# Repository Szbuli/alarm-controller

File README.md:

# Sensor Controller

## Main Features

- **15 configurable sensor inputs**  
- **Supported power supply:** 13.8 V nominal  
- **Home Assistant autodiscovery** via MQTT gateway
- **Input types supported:**  
  - Alarm sensors with multi-level signaling (e.g., open/tamper detection)  
  - Pulse counters (e.g., utility meters)

## Hardware

- **Microcontroller:** STM32F103R8T6  
- **Non-volatile memory:** MB85RC256V FRAM  
- **CAN Bus Transceiver:** SN65HVD230  
- **Electrical protection:**  
  - Overvoltage-protected inputs  
  - Overload protection circuitry  
- **Debug Interface:** Serial Wire Debug (SWD)

## Development Tools

- **PCB Design:** Autodesk EAGLE  
- **Firmware:** STM32CubeIDE (C via HAL / LL libraries)

## Setup
1. **Assign the device ID** via MQTT topic: `smarthome/alarm_controller/config`
2. **Configure sensor input types**
-- `1` → Alarm sensor
-- `3` → Pulse counter (normally open)
-- `4` → Pulse counter (normally closed)

## Sensor Connection & Security

To ensure reliable operation and tamper detection, each sensor input must be connected using a resistor for end-of-line (EOL) supervision.
The controller uses a voltage divider circuit to distinguish between different sensor states. The correct resistor value is essential for accurate detection:

- **Switch / Door Contact Sensors:**  
  Use a **40.2 kΩ** resistor in series with the sensor contact.  
- **Alarm Sensors:**  
  - **Normal (closed) signal:** ~40 kΩ total resistance  
  - **Alarm (open) signal:** ~140 kΩ total resistance

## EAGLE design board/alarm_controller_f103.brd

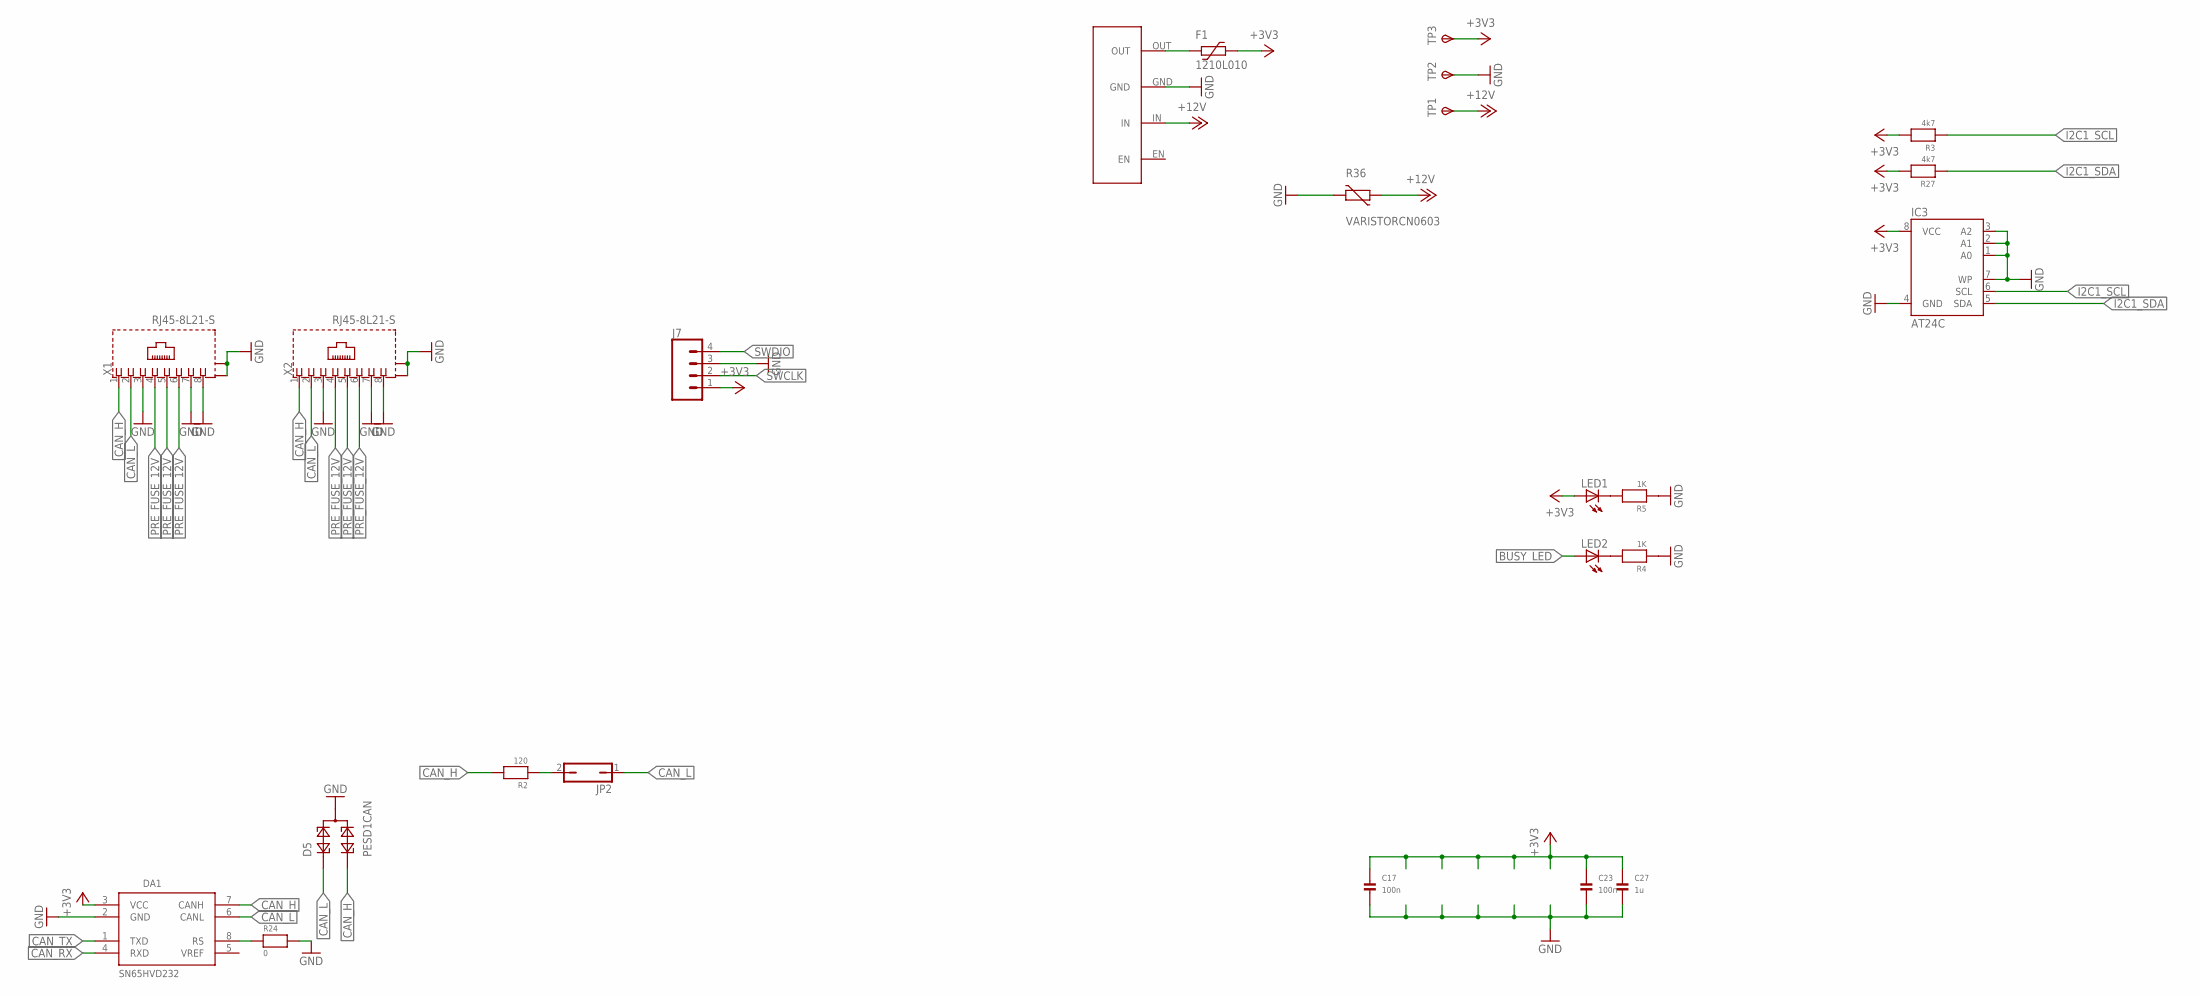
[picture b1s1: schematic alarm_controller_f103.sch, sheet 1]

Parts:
C17, C23: 100n; 0603
C27: 1u; 0603
D5: PESD1CAN; SOT23
DA1: SN65HVD232; SO08
F1: 1210L010; 1210L
IC3: AT24C; SOIC8
J7: CONN_04POLAR_LOCK; MOLEX-1X4_LOCK
JP2: JP1Q; JP1
LED1, LED2: LEDCHIPLED_0805; CHIPLED_0805
R2: 120; 0603
R3, R27: 4k7; 0603
R4, R5: 1K; 0603
R24: 0; 0603
R36: VARISTORCN0603; CT/CN0603
TP1, TP2, TP3: TPSTP20R; TP20R
U$4: HW-613
X1, X2: RJ45-8L21-S; RJ45-SHIELD1

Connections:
+3V3: C17.1, C23.1, C27.1, DA1.3 (VCC), F1.1, IC3.8 (VCC), J7.1, LED1.A, R3.2, R27.2, TP3.TP; also elsewhere on the board
+12V: R36.1, TP1.TP, U$4.IN; also elsewhere on the board
BUSY_LED: LED2.A; also elsewhere on the board
CAN_H: D5.2, DA1.7 (CANH), R2.2, X1.1, X2.1
CAN_L: D5.1, DA1.6 (CANL), JP2.1, X1.2, X2.2
CAN_RX: DA1.4 (RXD); also elsewhere on the board
CAN_TX: DA1.1 (TXD); also elsewhere on the board
GND: C17.2, C23.2, C27.2, D5.3, DA1.2 (GND), IC3.1 (A0), IC3.2 (A1), IC3.3 (A2), IC3.4 (GND), IC3.7 (WP), J7.3, R4.1, R5.1, R24.2, R36.2, TP2.TP, U$4.GND, X1.3, X1.7, X1.8, X1.S1 (S), X1.S2 (S), X2.3, X2.7, X2.8, X2.S1 (S), X2.S2 (S); also elsewhere on the board
I2C1_SCL: IC3.6 (SCL), R3.1; also elsewhere on the board
I2C1_SDA: IC3.5 (SDA), R27.1; also elsewhere on the board
unnamed: F1.2, U$4.OUT
unnamed: LED1.C, R5.2
unnamed: LED2.C, R4.2
unnamed: JP2.2, R2.1
unnamed: DA1.8 (RS), R24.1
PRE_FUSE_12V: X1.4, X1.5, X1.6, X2.4, X2.5, X2.6; also elsewhere on the board
SWCLK: J7.2; also elsewhere on the board
SWDIO: J7.4; also elsewhere on the board

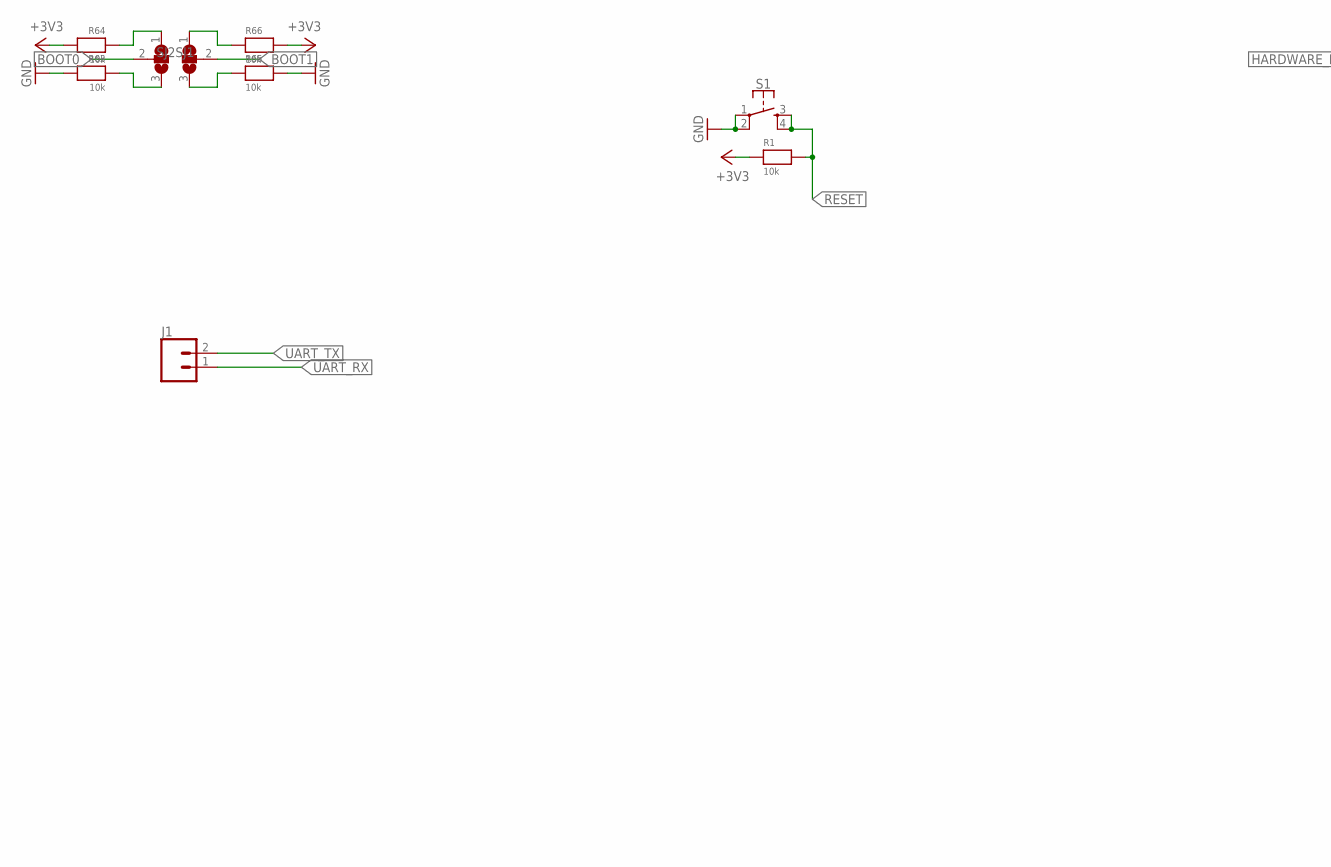
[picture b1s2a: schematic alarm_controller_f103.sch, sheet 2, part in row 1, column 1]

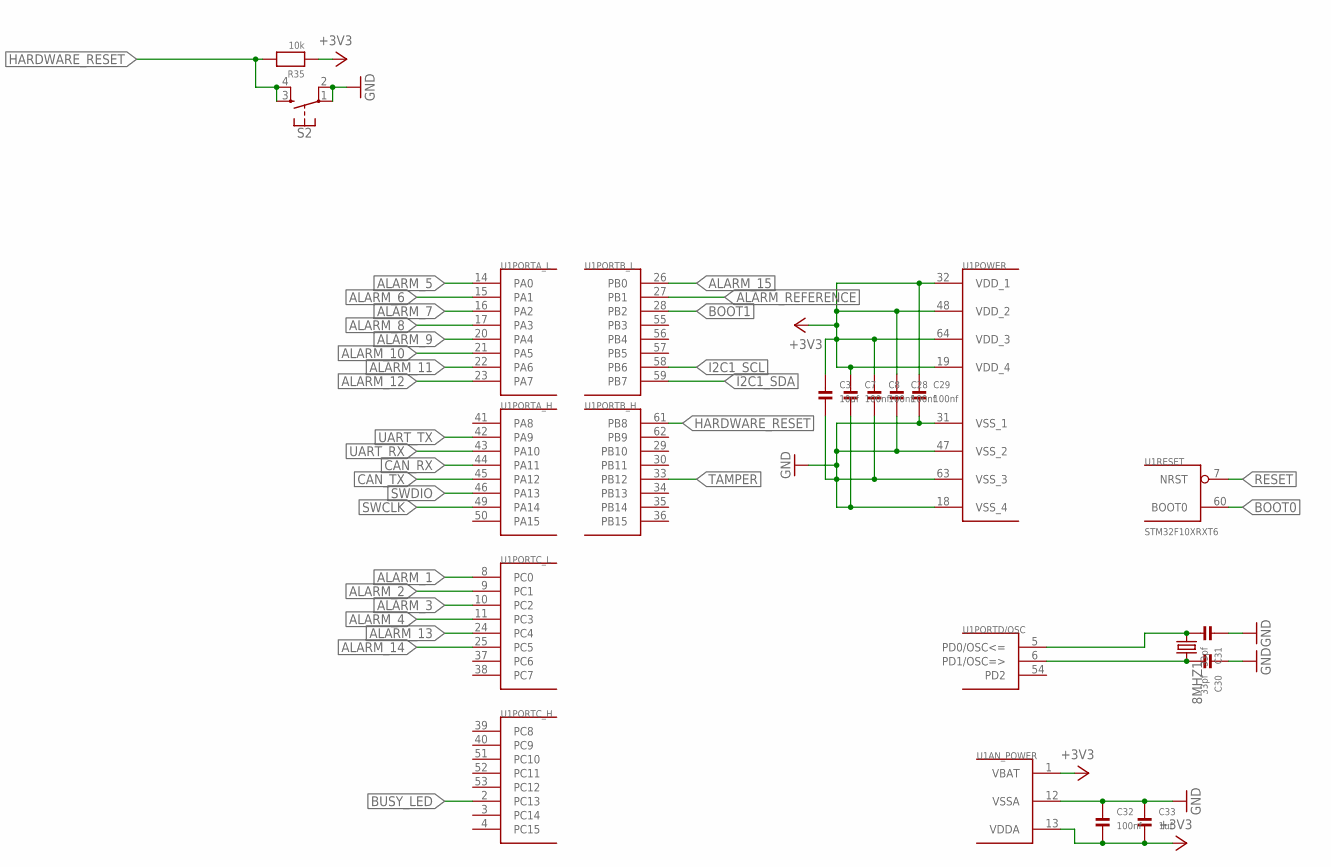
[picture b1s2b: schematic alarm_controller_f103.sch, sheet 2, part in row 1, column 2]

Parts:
8MHZ1: CRYSTALHC49UP; HC49UP
C3: 10uf; 0805
C7, C8, C28, C29, C32: 100nf; 0603-MINI
C30, C31: 33pf; 0603
C33: 1uf; 0603-MINI
J1: CONN_02; 1X02
R1, R35, R63, R64, R65, R66: 10k; 0603
S1, S2: MOMENTARY-SWITCH-SPST-2-SMD-4.6X2.8MM; TACTILE_SWITCH_SMD_4.6X2.8MM
SJ1, SJ2: SJ2W; SJ_2
U1: STM32F10XRXT6; TQFP64

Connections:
+3V3: C3.1, C7.1, C8.1, C28.1, C29.1, C32.2, C33.2, R1.1, R35.1, R64.2, R66.2, U1.1 (VBAT), U1.13 (VDDA), U1.19 (VDD_4), U1.32 (VDD_1), U1.48 (VDD_2), U1.64 (VDD_3); also elsewhere on the board
ALARM_1: U1.8 (PC0); also elsewhere on the board
ALARM_2: U1.9 (PC1); also elsewhere on the board
ALARM_3: U1.10 (PC2); also elsewhere on the board
ALARM_4: U1.11 (PC3); also elsewhere on the board
ALARM_5: U1.14 (PA0); also elsewhere on the board
ALARM_6: U1.15 (PA1); also elsewhere on the board
ALARM_7: U1.16 (PA2); also elsewhere on the board
ALARM_8: U1.17 (PA3); also elsewhere on the board
ALARM_9: U1.20 (PA4); also elsewhere on the board
ALARM_10: U1.21 (PA5); also elsewhere on the board
ALARM_11: U1.22 (PA6); also elsewhere on the board
ALARM_12: U1.23 (PA7); also elsewhere on the board
ALARM_13: U1.24 (PC4); also elsewhere on the board
ALARM_14: U1.25 (PC5); also elsewhere on the board
ALARM_15: U1.26 (PB0); also elsewhere on the board
ALARM_REFERENCE: U1.27 (PB1); also elsewhere on the board
BOOT0: SJ1.2, U1.60 (BOOT0)
BOOT1: SJ2.2, U1.28 (PB2)
BUSY_LED: U1.2 (PC13); also elsewhere on the board
CAN_RX: U1.44 (PA11); also elsewhere on the board
CAN_TX: U1.45 (PA12); also elsewhere on the board
GND: C3.2, C7.2, C8.2, C28.2, C29.2, C30.1, C31.1, C32.1, C33.1, R63.2, R65.2, S1.1, S1.2, S2.1, S2.2, U1.12 (VSSA), U1.18 (VSS_4), U1.31 (VSS_1), U1.47 (VSS_2), U1.63 (VSS_3); also elsewhere on the board
HARDWARE_RESET: R35.2, S2.3, S2.4, U1.61 (PB8)
I2C1_SCL: U1.58 (PB6); also elsewhere on the board
I2C1_SDA: U1.59 (PB7); also elsewhere on the board
unnamed: R66.1, SJ2.1
unnamed: R64.1, SJ1.1
unnamed: R65.1, SJ2.3
unnamed: R63.1, SJ1.3
unnamed: 8MHZ1.2, C30.2, U1.6 (PD1/OSC=>)
unnamed: 8MHZ1.1, C31.2, U1.5 (PD0/OSC<=)
RESET: R1.2, S1.3, S1.4, U1.7 (NRST)
SWCLK: U1.49 (PA14); also elsewhere on the board
SWDIO: U1.46 (PA13); also elsewhere on the board
TAMPER: U1.33 (PB12); also elsewhere on the board
UART_RX: J1.1, U1.43 (PA10)
UART_TX: J1.2, U1.42 (PA9)

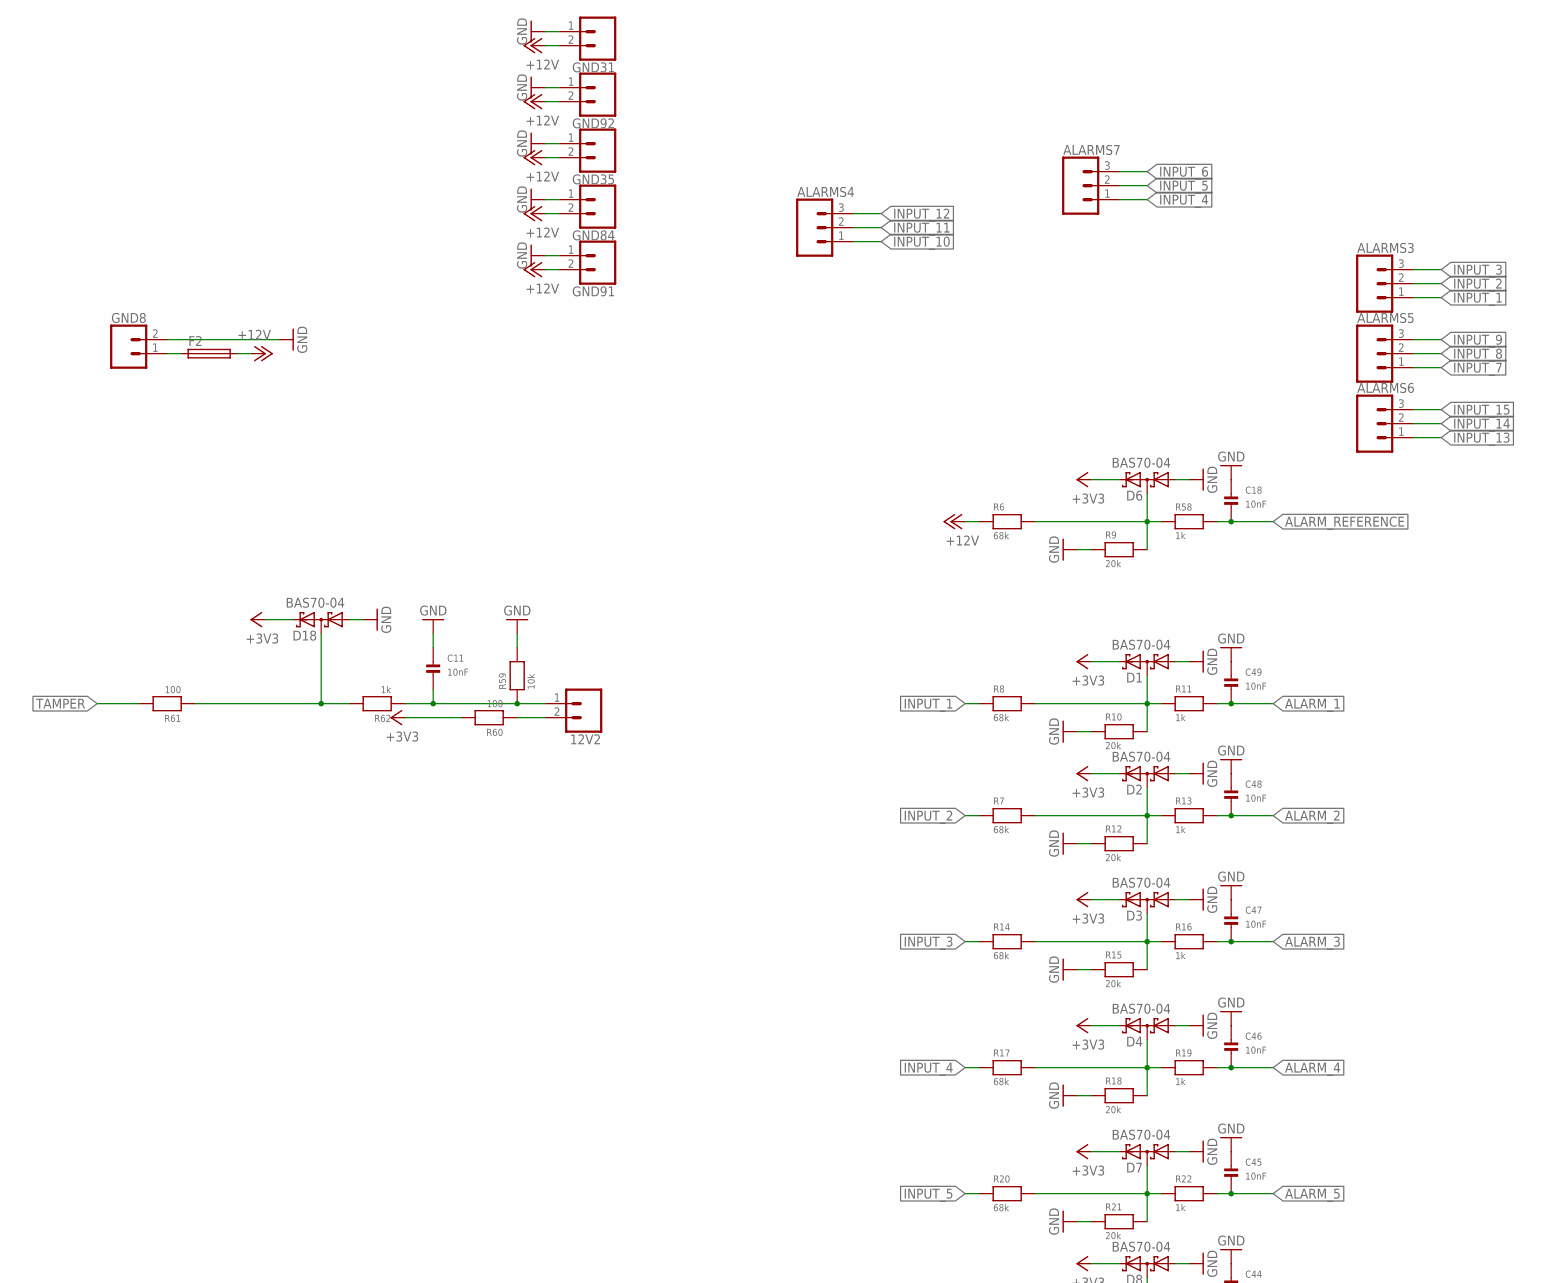
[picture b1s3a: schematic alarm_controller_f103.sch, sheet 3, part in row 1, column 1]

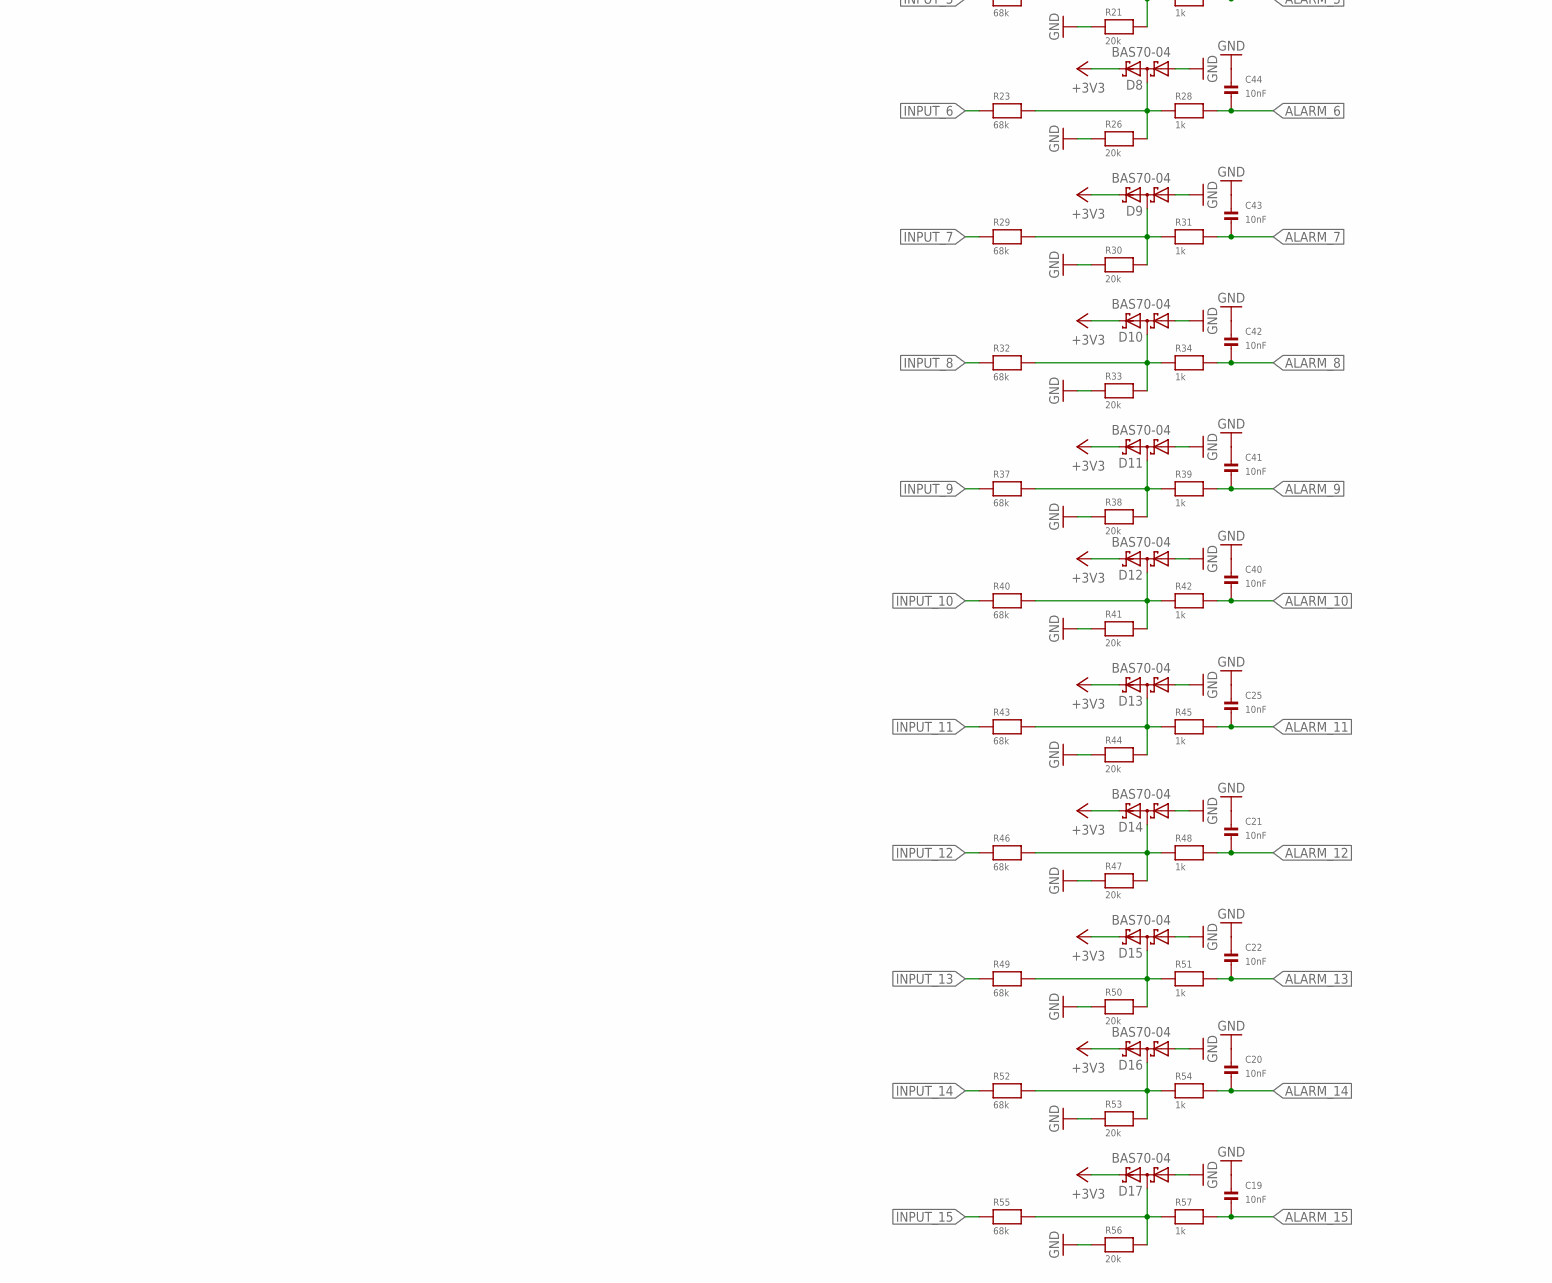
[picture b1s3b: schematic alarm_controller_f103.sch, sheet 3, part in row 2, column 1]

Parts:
12V2: CONN_023.5MM; SCREWTERMINAL-3.5MM-2
ALARMS3, ALARMS4, ALARMS5, ALARMS6, ALARMS7: CONN_03SCREW_LOCK; SCREWTERMINAL-3.5MM-3_LOCK.007S
C11, C18, C19, C20, C21, C22, C25, C40, C41, C42, C43, C44, C45, C46, C47, C48, C49: 10nF; 0603
D1, D2, D3, D4, D6, D7, D8, D9, D10, D11, D12, D13, D14, D15, D16, D17, D18: BAS70-04; SOT23
F2: TE5
GND8: CONN_025MM; SCREWTERMINAL-5MM-2
GND31, GND35, GND84, GND91, GND92: CONN_023.5MM; SCREWTERMINAL-3.5MM-2
R6, R7, R8, R14, R17, R20, R23, R29, R32, R37, R40, R43, R46, R49, R52, R55: 68k; 0603
R9, R10, R12, R15, R18, R21, R26, R30, R33, R38, R41, R44, R47, R50, R53, R56: 20k; 0603
R11, R13, R16, R19, R22, R28, R31, R34, R39, R42, R45, R48, R51, R54, R57, R58, R62: 1k; 0603
R59: 10k; 0603
R60, R61: 100; 0603

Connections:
12V_REFERENCE1: D2.3 (C1A2), R7.2, R12.2, R13.1
12V_REFERENCE2: D3.3 (C1A2), R14.2, R15.2, R16.1
12V_REFERENCE3: D4.3 (C1A2), R17.2, R18.2, R19.1
12V_REFERENCE4: D7.3 (C1A2), R20.2, R21.2, R22.1
12V_REFERENCE5: D8.3 (C1A2), R23.2, R26.2, R28.1
12V_REFERENCE6: D9.3 (C1A2), R29.2, R30.2, R31.1
12V_REFERENCE7: D10.3 (C1A2), R32.2, R33.2, R34.1
12V_REFERENCE8: D11.3 (C1A2), R37.2, R38.2, R39.1
12V_REFERENCE9: D12.3 (C1A2), R40.2, R41.2, R42.1
12V_REFERENCE10: D13.3 (C1A2), R43.2, R44.2, R45.1
12V_REFERENCE11: D14.3 (C1A2), R46.2, R47.2, R48.1
12V_REFERENCE12: D15.3 (C1A2), R49.2, R50.2, R51.1
12V_REFERENCE13: D16.3 (C1A2), R52.2, R53.2, R54.1
12V_REFERENCE14: D17.3 (C1A2), R55.2, R56.2, R57.1
+3V3: D1.2 (C2), D2.2 (C2), D3.2 (C2), D4.2 (C2), D6.2 (C2), D7.2 (C2), D8.2 (C2), D9.2 (C2), D10.2 (C2), D11.2 (C2), D12.2 (C2), D13.2 (C2), D14.2 (C2), D15.2 (C2), D16.2 (C2), D17.2 (C2), D18.2 (C2), R60.2; also elsewhere on the board
+12V: F2.2, GND31.2, GND35.2, GND84.2, GND91.2, GND92.2, R6.1; also elsewhere on the board
A23: D6.3 (C1A2), R6.2, R9.2, R58.1
ALARM_1: C49.2, R11.2; also elsewhere on the board
ALARM_2: C48.2, R13.2; also elsewhere on the board
ALARM_3: C47.2, R16.2; also elsewhere on the board
ALARM_4: C46.2, R19.2; also elsewhere on the board
ALARM_5: C45.2, R22.2; also elsewhere on the board
ALARM_6: C44.2, R28.2; also elsewhere on the board
ALARM_7: C43.2, R31.2; also elsewhere on the board
ALARM_8: C42.2, R34.2; also elsewhere on the board
ALARM_9: C41.2, R39.2; also elsewhere on the board
ALARM_10: C40.2, R42.2; also elsewhere on the board
ALARM_11: C25.2, R45.2; also elsewhere on the board
ALARM_12: C21.2, R48.2; also elsewhere on the board
ALARM_13: C22.2, R51.2; also elsewhere on the board
ALARM_14: C20.2, R54.2; also elsewhere on the board
ALARM_15: C19.2, R57.2; also elsewhere on the board
ALARM_REFERENCE: C18.2, R58.2; also elsewhere on the board
ASD: D1.3 (C1A2), R8.2, R10.2, R11.1
ASDASD: D18.3 (C1A2), R61.1, R62.2
GND: C11.1, C18.1, C19.1, C20.1, C21.1, C22.1, C25.1, C40.1, C41.1, C42.1, C43.1, C44.1, C45.1, C46.1, C47.1, C48.1, C49.1, D1.1 (A1), D2.1 (A1), D3.1 (A1), D4.1 (A1), D6.1 (A1), D7.1 (A1), D8.1 (A1), D9.1 (A1), D10.1 (A1), D11.1 (A1), D12.1 (A1), D13.1 (A1), D14.1 (A1), D15.1 (A1), D16.1 (A1), D17.1 (A1), D18.1 (A1), GND8.2, GND31.1, GND35.1, GND84.1, GND91.1, GND92.1, R9.1, R10.1, R12.1, R15.1, R18.1, R21.1, R26.1, R30.1, R33.1, R38.1, R41.1, R44.1, R47.1, R50.1, R53.1, R56.1, R59.2; also elsewhere on the board
INPUT_1: ALARMS3.1, R8.1
INPUT_2: ALARMS3.2, R7.1
INPUT_3: ALARMS3.3, R14.1
INPUT_4: ALARMS7.1, R17.1
INPUT_5: ALARMS7.2, R20.1
INPUT_6: ALARMS7.3, R23.1
INPUT_7: ALARMS5.1, R29.1
INPUT_8: ALARMS5.2, R32.1
INPUT_9: ALARMS5.3, R37.1
INPUT_10: ALARMS4.1, R40.1
INPUT_11: ALARMS4.2, R43.1
INPUT_12: ALARMS4.3, R46.1
INPUT_13: ALARMS6.1, R49.1
INPUT_14: ALARMS6.2, R52.1
INPUT_15: ALARMS6.3, R55.1
unnamed: 12V2.2, R60.1
unnamed: 12V2.1, C11.2, R59.1, R62.1
PRE_FUSE_12V: F2.1, GND8.1; also elsewhere on the board
TAMPER: R61.2; also elsewhere on the board

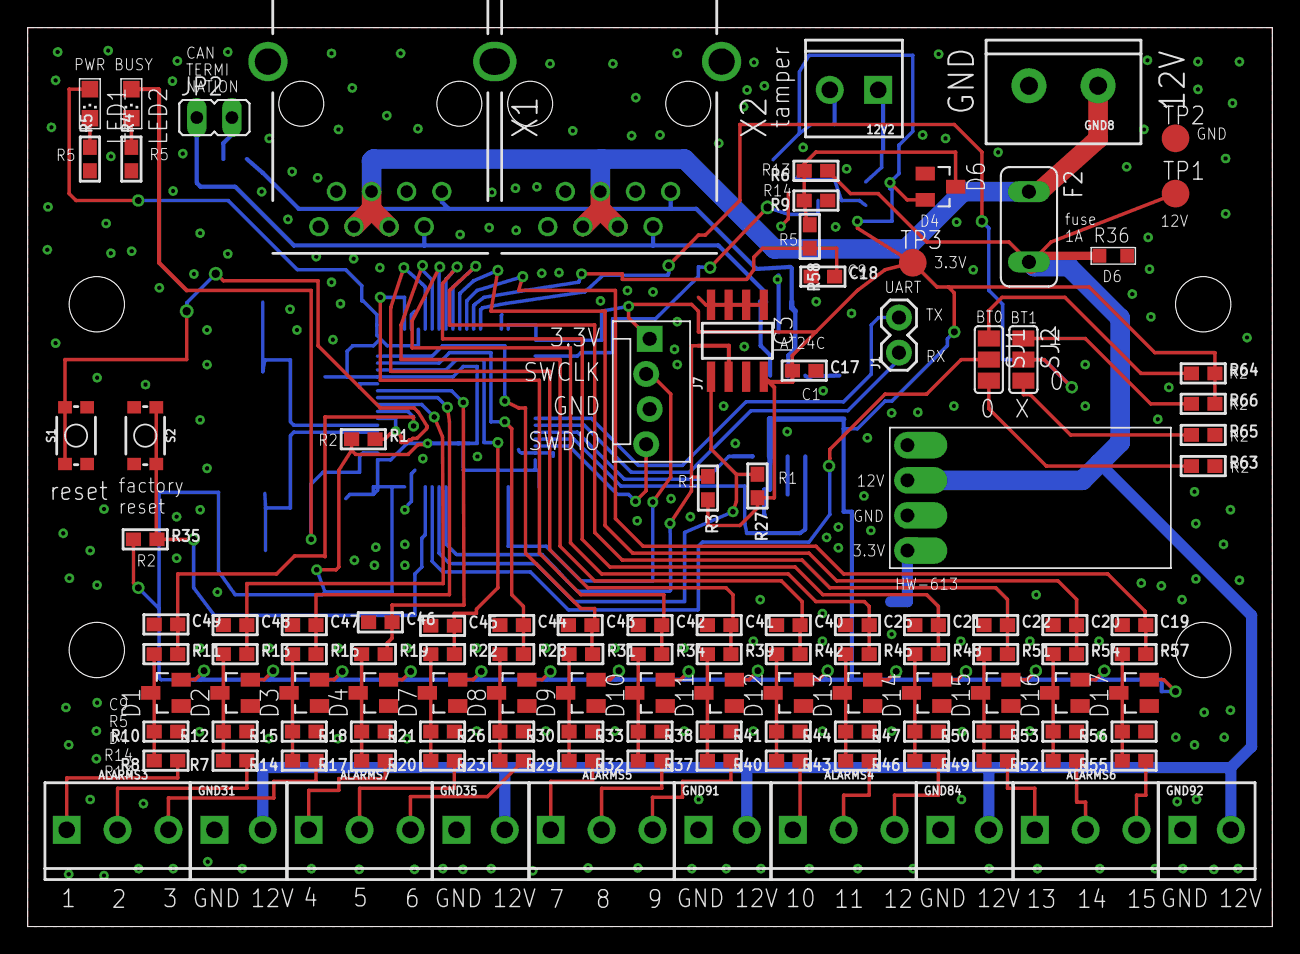
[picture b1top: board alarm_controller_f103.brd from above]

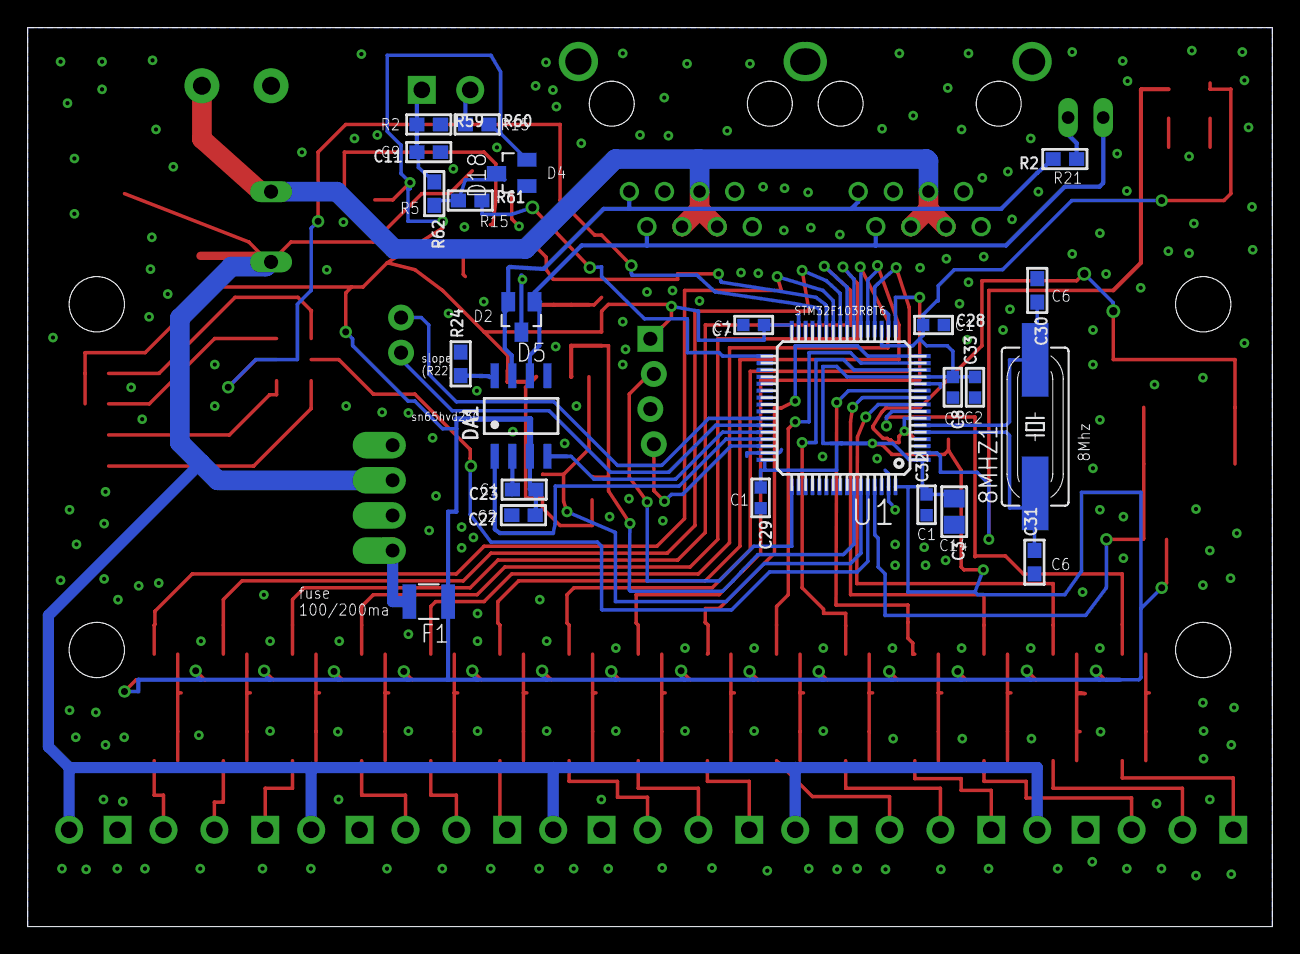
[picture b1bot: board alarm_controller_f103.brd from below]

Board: 2 copper layers, 90.0 x 65.0 mm, 147 parts (24 on the bottom side), 81 nets.

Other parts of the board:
U$5, U$6: C45-DIN-MOUNT-2-HOLE

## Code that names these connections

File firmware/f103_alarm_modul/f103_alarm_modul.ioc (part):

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Mcu.Name=STM32F103R(8-B)Tx
Mcu.Package=LQFP64
Mcu.UserName=STM32F103R8Tx
PA0-WKUP.GPIOParameters=GPIO_Label
PA0-WKUP.GPIO_Label=ALARM_5
PA0-WKUP.Signal=ADCx_IN0
PA1.GPIOParameters=GPIO_Label
PA1.GPIO_Label=ALARM_6
PA1.Signal=ADCx_IN1
PA10.Mode=Asynchronous
PA10.Signal=USART1_RX
PA11.Mode=CAN_Activate
PA11.Signal=CAN_RX
PA12.Mode=CAN_Activate
PA12.Signal=CAN_TX
PA13.Mode=Serial_Wire
PA13.Signal=SYS_JTMS-SWDIO
PA14.Mode=Serial_Wire
PA14.Signal=SYS_JTCK-SWCLK
PA2.GPIOParameters=GPIO_Label
PA2.GPIO_Label=ALARM_7
PA2.Signal=ADCx_IN2
PA3.GPIOParameters=GPIO_Label
PA3.GPIO_Label=ALARM_8
PA3.Signal=ADCx_IN3
PA4.GPIOParameters=GPIO_Label
PA4.GPIO_Label=ALARM_9
PA4.Signal=ADCx_IN4
PA5.GPIOParameters=GPIO_Label
PA5.GPIO_Label=ALARM_10
PA5.Signal=ADCx_IN5
PA6.GPIOParameters=GPIO_Label
PA6.GPIO_Label=ALARM_11
PA6.Signal=ADCx_IN6
PA7.GPIOParameters=GPIO_Label
PA7.GPIO_Label=ALARM_12
PA7.Signal=ADCx_IN7
PA9.Mode=Asynchronous
PA9.Signal=USART1_TX
PB0.GPIOParameters=GPIO_Label
PB0.GPIO_Label=ALARM_15
PB0.Signal=ADCx_IN8
PB1.GPIOParameters=GPIO_Label
PB1.GPIO_Label=ALARM_12V_REFERENCE
PB1.Signal=ADCx_IN9
PB12.GPIOParameters=GPIO_Label
PB12.GPIO_Label=TAMPER
PB12.Signal=GPXTI12
PB2.GPIOParameters=GPIO_Label
PB2.GPIO_Label=BOOOOT2
PB2.Signal=GPIO_Input
PB6.GPIOParameters=GPIO_Pu
PB6.GPIO_Pu=GPIO_PULLUP
PB6.Mode=I2C
PB6.Signal=I2C1_SCL
PB7.GPIOParameters=GPIO_Pu
PB7.GPIO_Pu=GPIO_PULLUP
PB7.Mode=I2C
PB7.Signal=I2C1_SDA
PB8.GPIOParameters=GPIO_Label
PB8.GPIO_Label=FACTORY_RESET
PB8.Signal=GPIO_Input
PC0.GPIOParameters=GPIO_Label
PC0.GPIO_Label=ALARM_1
PC0.Signal=ADCx_IN10
PC1.GPIOParameters=GPIO_Label
PC1.GPIO_Label=ALARM_2
PC1.Signal=ADCx_IN11
PC13-TAMPER-RTC.GPIOParameters=PinState,GPIO_Label
PC13-TAMPER-RTC.GPIO_Label=BUSY_LED
PC13-TAMPER-RTC.PinState=GPIO_PIN_SET
PC13-TAMPER-RTC.Signal=GPIO_Output
PC2.GPIOParameters=GPIO_Label
PC2.GPIO_Label=ALARM_3
PC2.Signal=ADCx_IN12
PC3.GPIOParameters=GPIO_Label
PC3.GPIO_Label=ALARM_4
PC3.Signal=ADCx_IN13
PC4.GPIOParameters=GPIO_Label
PC4.GPIO_Label=ALARM_13
PC4.Signal=ADCx_IN14
PC5.GPIOParameters=GPIO_Label
PC5.GPIO_Label=ALARM_14
PC5.Signal=ADCx_IN15
PD0-OSC_IN.Mode=HSE-External-Oscillator
PD0-OSC_IN.Signal=RCC_OSC_IN
PD1-OSC_OUT.Mode=HSE-External-Oscillator
PD1-OSC_OUT.Signal=RCC_OSC_OUT
RCC.SYSCLKFreq_VALUE=72000000
RCC.SYSCLKSource=RCC_SYSCLKSOURCE_PLLCLK
board=custom

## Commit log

2020-04-21 add board
2020-05-01 init fw
2020-05-02 change to premade power supply
2020-05-03 change mounting to lib version
2020-05-08 board - minor adjustments
2020-05-08 update logo
2020-05-08 add reset button
2020-05-09 fix tamper
2020-05-10 add support for hardware factory reset
2020-05-10 update uart logging
2020-05-11 make tamper configurable
2020-05-11 update can id names
2020-06-11 power over can
2020-06-11 fix hardware reset state
2020-06-12 update board labels
2020-06-23 add heartbeat
2020-06-29 add varistor
2020-07-02 increase 12v and gnd connections
2020-07-13 refresh eagle libs
2020-07-18 jumpers for boot mode
2020-07-18 fix labels
2020-07-18 change to solderable boot jumper
2020-08-23 increase heartbeat interval
2020-11-23 change to microfit from rj45
2020-11-24 change tamper output to regular 3.5mm screw terminal
2020-12-02 redesign voltage divider circuits
2020-12-03 update labels
2020-12-03 set default boot mode label
2021-01-03 clean up adc code
2021-01-03 migrate project to cubeide
2021-01-03 clean up some warnings
2021-01-03 clean up warnings
2021-01-05 init
2021-01-10 fix board cfg
2021-01-10 fix flag
2021-02-21 wait on queue when tx mailbox is full
2021-02-28 fix can send
2021-02-28 update fw to V1.25.2 (#2)
2021-02-28 update some labels, fix can L and H mixup
2021-02-28 add labels for ics
2021-02-28 pwr led should be left
2021-02-28 add default value for slope resistor
2021-03-07 fix can init order
2021-03-11 change back to rj45 (from microfit)
2021-03-11 more distance between rj45 connectors
2021-03-12 fix some labels
2021-03-13 change to packages with place drawing
2021-03-13 change deprecated labels
2021-03-14 swap pwr input for correct orientation
2021-06-14 basic ioc config
2021-06-14 init firmware
2021-06-14 add external crystal
2021-06-16 change to new ic
2021-07-10 fix ioc config
2021-07-10 fix can bus speed
2021-07-11 change task prios
2021-07-11 ignore launch
2021-07-11 heartbeat enabled by default
2021-08-13 fine tune heartbeat
2021-08-13 trigger heartbeat on first iteration
2021-10-24 move to f103 (#3)
    * basic ioc config
    * init firmware
    * add external crystal
    * change to new ic
    * fix some labels
    * fix ioc config
2021-10-24 add ha status config
2021-10-26 add ha status config (#4)
2021-11-13 add 3.3v to swd connector
2024-09-28 update hal
2024-10-18 update hal (#7)
2024-10-23 add pulse counter
2024-10-24 add pulse counter (#8)
2025-06-29 add initial value for counter
2025-06-30 increase can queue size
2025-06-30 fix topic
2025-06-30 Feature/counter no pulse (#9)
    * add initial value for counter
    * increase can queue size
    * fix topic
2025-07-03 clear topic if not relevant
2025-07-03 do not flood canbus
2025-07-03 fix wrong topic
2025-07-03 fix memory address
2025-07-04 Bugfix/set count ha discovery (#10)
    * clear topic if not relevant
    * do not flood canbus
    * fix wrong topic
    * fix memory address

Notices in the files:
parts and their libraries:
SparkFun-Connectors: Licensing: Creative Commons ShareAlike 4.0 International - https://creativecommons.org/licenses/by-sa/4.0
microbuilder: This work is placed in the public domain, and may be freely used for commercial and non-commercial work with the following conditions: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
